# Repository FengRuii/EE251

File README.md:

# EE251

Various Designs for EE251 Winter @ Stanford

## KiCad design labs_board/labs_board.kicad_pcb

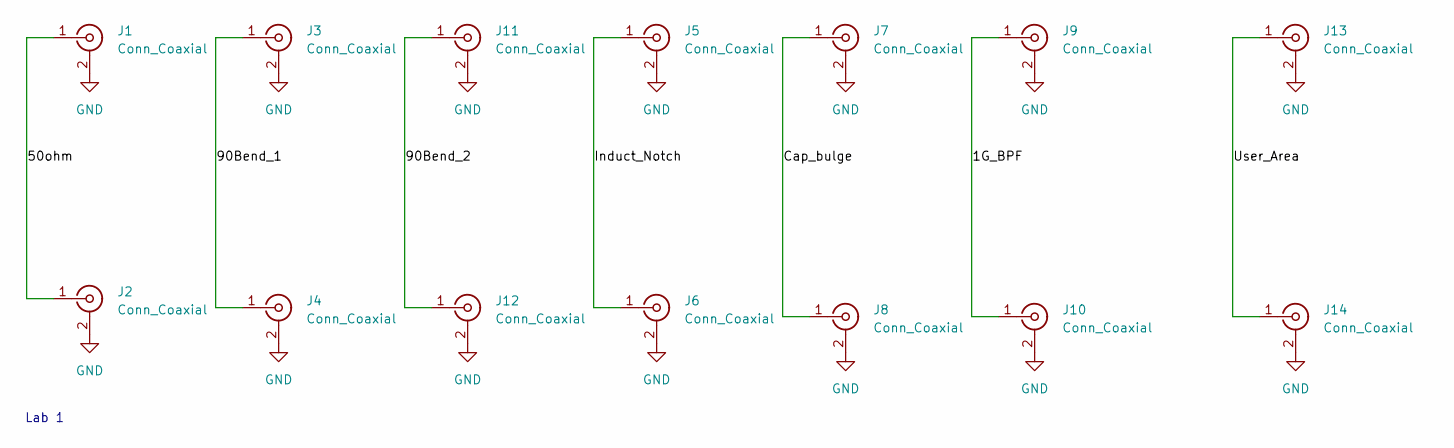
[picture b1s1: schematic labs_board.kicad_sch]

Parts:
J1, J2, J3, J4, J5, J6, J7, J8, J9, J10, J11, J12, J13, J14: Conn_Coaxial; BNC_TEConnectivity_1478204_Vertical

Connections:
/1G_BPF: J9.1 (In), J10.1 (In)
/50ohm: J1.1 (In), J2.1 (In)
/90Bend_1: J3.1 (In), J4.1 (In)
/90Bend_2: J11.1 (In), J12.1 (In)
/Cap_bulge: J7.1 (In), J8.1 (In)
/Induct_Notch: J5.1 (In), J6.1 (In)
/User_Area: J13.1 (In), J14.1 (In)
GND: J1.2 (Ext), J2.2 (Ext), J3.2 (Ext), J4.2 (Ext), J5.2 (Ext), J6.2 (Ext), J7.2 (Ext), J8.2 (Ext), J9.2 (Ext), J10.2 (Ext), J11.2 (Ext), J12.2 (Ext), J13.2 (Ext), J14.2 (Ext)

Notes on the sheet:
Lab 1

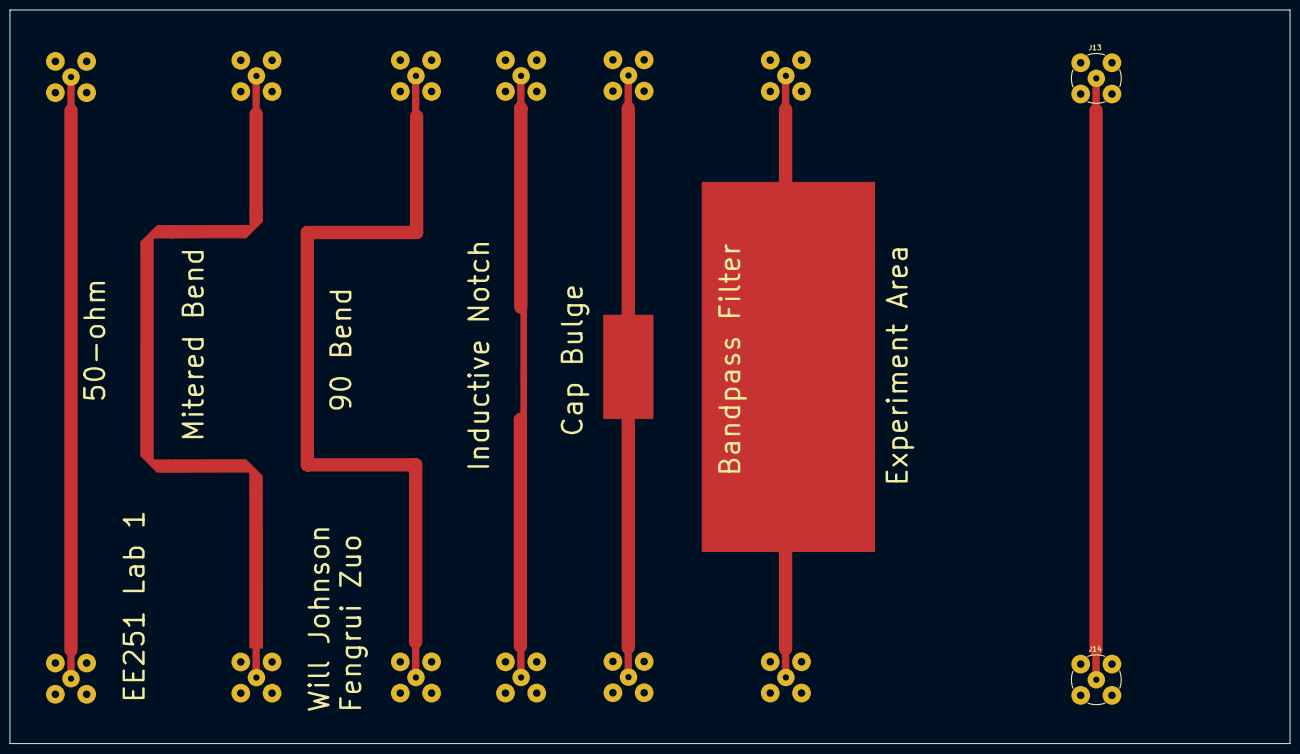
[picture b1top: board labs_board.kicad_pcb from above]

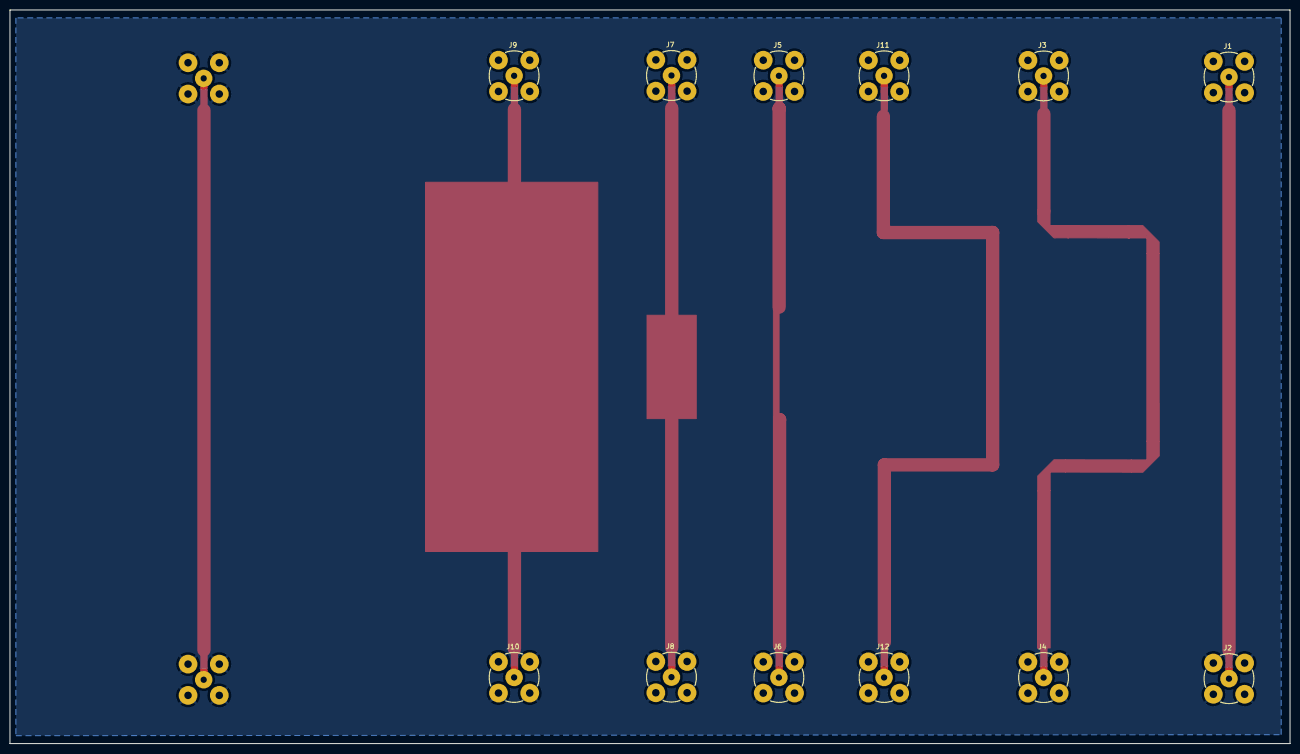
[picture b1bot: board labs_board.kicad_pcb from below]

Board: 2 copper layers, 260.0 x 149.0 mm, 14 parts (12 on the bottom side), 8 nets.

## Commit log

2025-01-26 Lab 1 commit
2025-01-26 second update
2025-01-26 third update
2025-01-26 4th updatee
2025-01-26 4th update
